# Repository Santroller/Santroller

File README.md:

# The Santroller Platform
The Santroller platform provides the ability to program micro controllers that emulate various rhythm game controllers for computers and various consoles. This is done using the Santroller Configurator, which can program various microcontrollers to emulate different controllers.

Documentation can be found at https://santroller.tangentmc.net/

## Firmware update integrity

OTA images include a 256-byte trailer: 224 zero bytes followed by the SHA-256 digest of
the preceding application bytes. Firmware verifies the staged image before marking it
valid and rebooting into the update. Raw application binaries without this trailer are
not valid OTA inputs; use the generated `santroller_fota_image.bin` or the configurator's
packaged OTA image. Automatic secondary-Pico updates generate the same trailer from
the running application.

The configurator requires a one-time UF2 update for installed builds before 3493, which first
enabled verification. Firmware without a build number must report image verification support
instead. Subsequent updates can use verified OTA images.
This detects accidental corruption, not image authenticity or hardware compatibility.

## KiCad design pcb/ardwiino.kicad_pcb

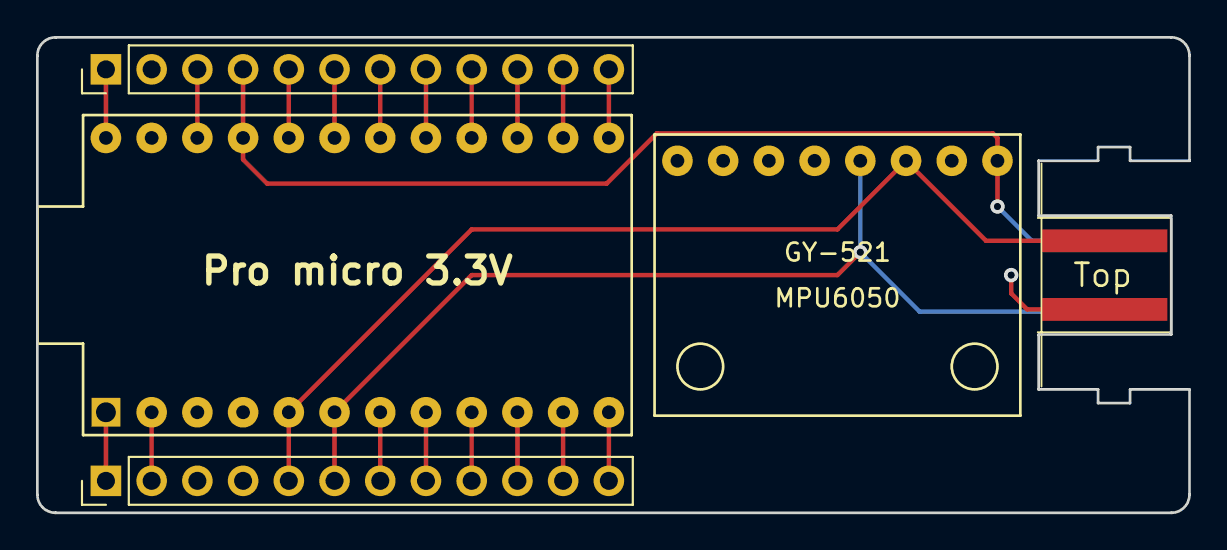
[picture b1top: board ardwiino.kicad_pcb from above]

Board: 2 copper layers, 64.0 x 26.4 mm, 5 parts (0 on the bottom side), 22 nets.

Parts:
M1: Top; HHJ-NUNCHUCK-LOCK
MPU6050: GY-521; GY521
ProMicro_Left1: Conn_01x12; PinHeader_1x12_P2.54mm_Vertical
ProMicro_Right1: Conn_01x12; PinHeader_1x12_P2.54mm_Vertical
U1: ProMicro

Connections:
+3V3: M1.3.3V, MPU6050.1, ProMicro_Right1.4, U1.21
/B1: ProMicro_Right1.9, U1.16
/B2: ProMicro_Right1.11, U1.14
/B3: ProMicro_Right1.10, U1.15
/B4: ProMicro_Left1.11, U1.11
/B5: ProMicro_Left1.12, U1.12
/B6: ProMicro_Right1.12, U1.13
/C6: ProMicro_Left1.8, U1.8
/D4: ProMicro_Left1.7, U1.7
/D7: ProMicro_Left1.9, U1.9
/E6: ProMicro_Left1.10, U1.10
/F4: ProMicro_Right1.5, U1.20
/F5: ProMicro_Right1.6, U1.19
/F6: ProMicro_Right1.7, U1.18
/F7: ProMicro_Right1.8, U1.17
/RAW: ProMicro_Right1.1, U1.24
/RST: ProMicro_Right1.3, U1.22
/RX: ProMicro_Left1.2, U1.2
/SCL: M1.CLK, MPU6050.3, ProMicro_Left1.5, U1.5
/SDA: M1.DATA, MPU6050.4, ProMicro_Left1.6, U1.6
/TX: ProMicro_Left1.1, U1.1
GND: M1.GND, MPU6050.2, ProMicro_Left1.3, ProMicro_Left1.4, ProMicro_Right1.2, U1.3, U1.4, U1.23
